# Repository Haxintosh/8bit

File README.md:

# 8bit
8-bit SAP-3 inspired breadboard CPU architecture design using 74xx series logic chips.  
## Files
KiCad design files can be found under `schematic/`, clone and open `8bit.kicad_pro`.  
Schematic PDF is under `schematic/pdf/`.  

Simulation files for Digital can be found under `simulation/`.  
The hex files to program EEPROMs are under `simulation/hex/`.  

Python code to generate ucode bin files is under `code/`, run the `code/generate_roms.py` to generate the files.  

A simple assembly code is under `code/examples/`.  

## Simulation
The project uses the `hneemann/Digital` [Digital](https://github.com/hneemann/digital) simulator.  
Open the `main_manual.dig` in Digital to view the simulation.  
  
Run the simulation and click on the AUTO_EN input for the clock to tick automatically, or you can also click the clock to pulse it manually.  

## Features
- 8 bit wide data bus
- 16 bit wide address bus
- 8 bit A/B/C/D/E/H/L/temporary registers
- BC, DE, HL can pair up to become a 16 bit wide register
- 32k RAM
- Memory-Mapped IO
- 16 bit stack pointer, memory address register, program counter
- 8080-like instruction set
- CompactFlash read/write
- LCD output

## Demo
1. SAP-3 in simulation

2. (Video) SAP-3 running fibonacci code

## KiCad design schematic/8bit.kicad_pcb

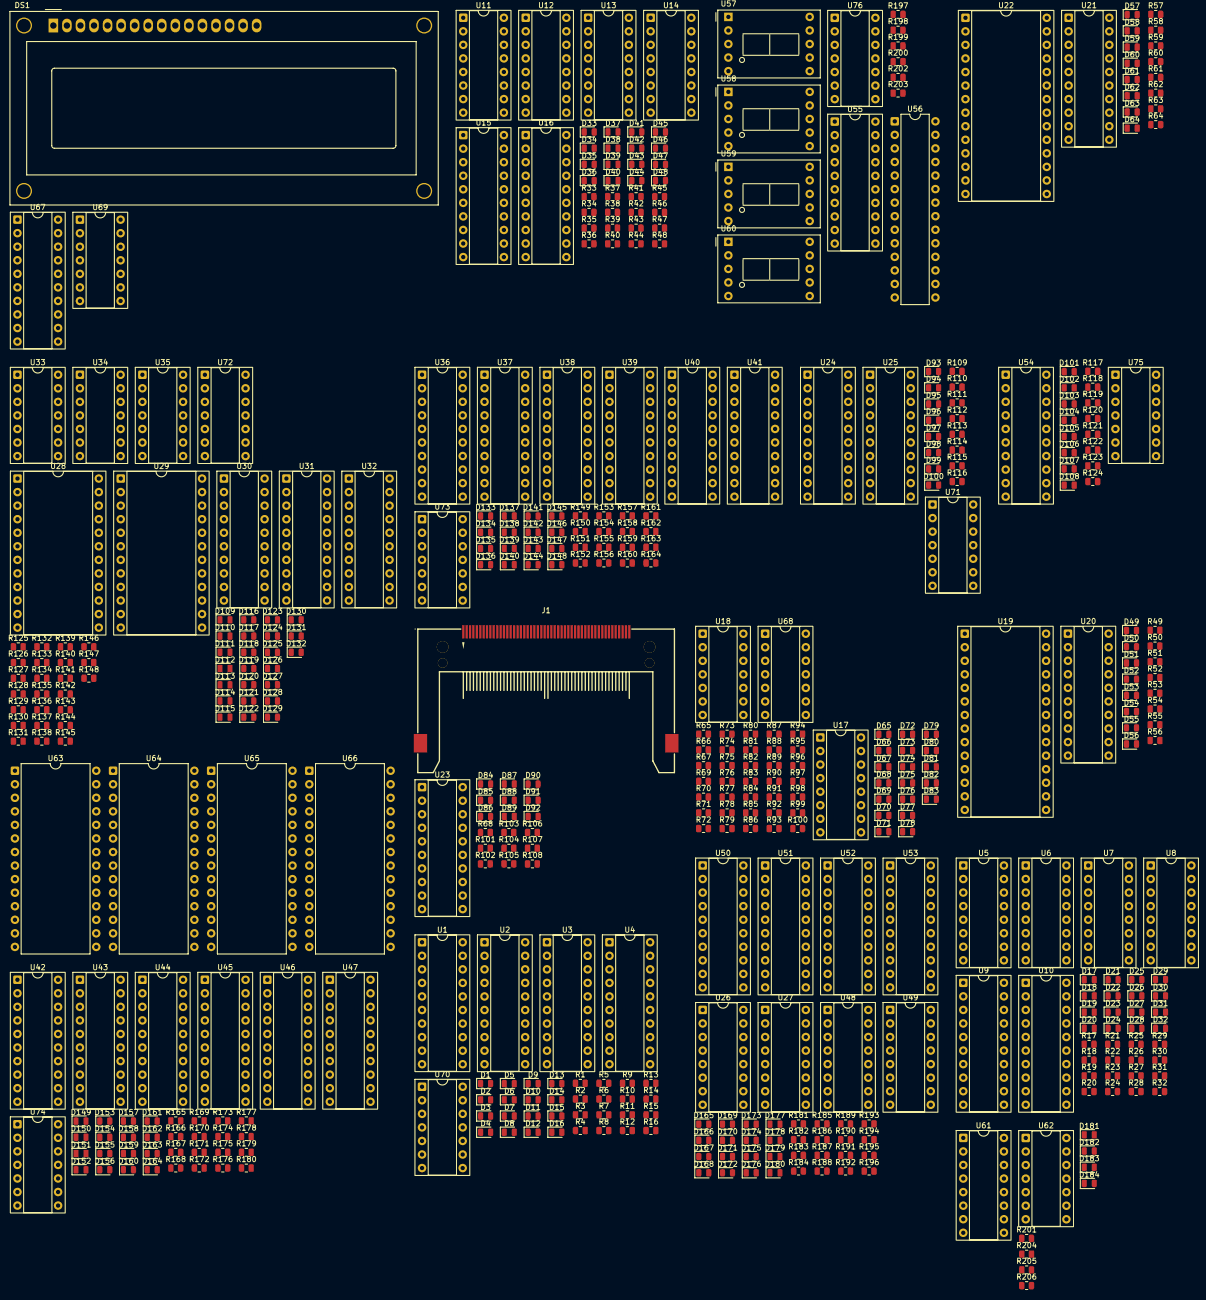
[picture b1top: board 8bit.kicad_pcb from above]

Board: 2 copper layers, 468 parts (0 on the bottom side), 560 nets, no tracks yet.

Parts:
D1, D2, D3, D4, D5, D6, D7, D8, D9, D10, D11, D12, D13, D14, D15, D16, D17, D18, D19, D20, D21, D22, D23, D24, D25, D26, D27, D28, D29, D30, D31, D32, D33, D34, D35, D36, D37, D38, D39, D40, D41, D42, D43, D44, D45, D46, D47, D48, D49, D50, D51, D52, D53, D54, D55, D56, D57, D58, D59, D60, D61, D62, D63, D64, D65, D66, D67, D68, D69, D70, D71, D72, D73, D74, D75, D76, D77, D78, D79, D80, D81, D82, D83, D84, D85, D86, D87, D88, D89, D90, D91, D92, D93, D94, D95, D96, D97, D98, D99, D100, D101, D102, D103, D104, D105, D106, D107, D108, D109, D110, D111, D112, D113, D114, D115, D116, D117, D118, D119, D120, D121, D122, D123, D124, D125, D126, D127, D128, D129, D130, D131, D132, D133, D134, D135, D136, D137, D138, D139, D140, D141, D142, D143, D144, D145, D146, D147, D148, D149, D150, D151, D152, D153, D154, D155, D156, D157, D158, D159, D160, D161, D162, D163, D164, D165, D166, D167, D168, D169, D170, D171, D172, D173, D174, D175, D176, D177, D178, D179, D180, D181, D182, D183, D184: LED; LED_0805_2012Metric
DS1: WC1602A
J1: CF; CONN-SMD_HYCW01-CF50-395B
R1, R2, R3, R4, R5, R6, R7, R8, R9, R10, R11, R12, R13, R14, R15, R16, R17, R18, R19, R20, R21, R22, R23, R24, R25, R26, R27, R28, R29, R30, R31, R32, R33, R34, R35, R36, R37, R38, R39, R40, R41, R42, R43, R44, R45, R46, R47, R48, R49, R50, R51, R52, R53, R54, R55, R56, R57, R58, R59, R60, R61, R62, R63, R64, R65, R66, R67, R68, R70, R72, R74, R76, R78, R80, R82, R84, R86, R88, R90, R92, R94, R96, R98, R100, R101, R102, R103, R104, R105, R106, R107, R108, R109, R110, R111, R112, R113, R114, R115, R116, R117, R118, R119, R120, R121, R122, R123, R124, R125, R126, R127, R128, R129, R130, R131, R132, R133, R134, R135, R136, R137, R138, R139, R140, R141, R142, R143, R144, R145, R146, R147, R148, R149, R150, R151, R152, R153, R154, R155, R156, R157, R158, R159, R160, R161, R162, R163, R164, R165, R166, R167, R168, R169, R170, R171, R172, R173, R174, R175, R176, R177, R178, R179, R180, R181, R182, R183, R184, R185, R186, R187, R188, R189, R190, R191, R192, R193, R194, R195, R196, R201, R204, R205, R206: 470; R_0805_2012Metric
R69, R71, R73, R75, R77, R79, R81, R83, R85, R87, R89, R91, R93, R95, R97, R99: 1k; R_0805_2012Metric
R197, R198, R199, R200, R202: 0; R_0805_2012Metric
R203: 4.7k; R_0805_2012Metric
U1, U2, U24, U32, U36, U38, U42, U43, U54, U55, U67: 74LS573; DIP-20_W7.62mm_Socket
U3, U4, U9, U10, U15, U16, U20, U21, U23, U25, U30, U37, U39, U40, U41, U44, U45, U46, U47, U50, U51, U52, U53: 74LS245; DIP-20_W7.62mm_Socket
U5, U6, U7, U8, U61: 74LS161; DIP-16_W7.62mm_Socket
U11, U12, U13, U14, U26, U27, U48, U49: 74LS193; DIP-16_W7.62mm_Socket
U17: 74LS138; DIP-16_W7.62mm_Socket
U18: 74LS20; DIP-14_W7.62mm_Socket
U19: HM62256BLP; DIP-28_W15.24mm_Socket
U22: KM28C64A; DIP-28_W15.24mm_Socket
U28, U29: 74LS181; DIP-24_W15.24mm_Socket
U31: 74LS373; DIP-20_W7.62mm_Socket
U33, U69, U70, U71, U72, U73, U74, U75, U76: 74LS08; DIP-14_W7.62mm_Socket
U34, U62: 74LS02; DIP-14_W7.62mm_Socket
U35: 74LS04; DIP-14_W7.62mm_Socket
U56: ATmega328-P; DIP-28_W7.62mm
U57, U58, U59, U60: D198K; D1X8K
U63, U64, U65, U66: 27C512; DIP-28_W15.24mm
U68: 74LS00; DIP-14_W7.62mm_Socket

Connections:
+5V: DS1.2 (VDD), DS1.15 (LED(+)), J1.13 (VCC), J1.32 (~CS1), J1.36 (~WE), J1.38 (VCC), R65.1, R66.1, R67.1, R203.1, U1.20 (VCC), U2.20 (VCC), U3.1 (A->B), U3.20 (VCC), U4.1 (A->B), U4.20 (VCC), U5.10 (CET), U5.16 (VCC), U6.16 (VCC), U7.16 (VCC), U8.16 (VCC), U9.1 (A->B), U9.20 (VCC), U10.1 (A->B), U10.20 (VCC), U11.16 (VCC), U12.16 (VCC), U13.16 (VCC), U14.16 (VCC), U15.1 (A->B), U15.20 (VCC), U16.1 (A->B), U16.20 (VCC), U17.6 (E3), U17.16 (VCC), U18.14 (VCC), U19.28 (VCC), U20.20 (VCC), U21.1 (A->B), U21.20 (VCC), U22.27 (~WE), U22.28 (VCC), U23.20 (VCC), U24.20 (VCC), U25.1 (A->B), U25.20 (VCC), U26.16 (VCC), U27.16 (VCC), U28.7 (Cn), U28.24 (VCC), U29.24 (VCC), U30.1 (A->B), U30.20 (VCC), U31.20 (VCC), U32.20 (VCC), U34.14 (VCC), U35.14 (VCC), U36.20 (VCC), U37.1 (A->B), U37.20 (VCC), U38.20 (VCC), U39.1 (A->B), U39.20 (VCC), U40.1 (A->B), U40.20 (VCC), U41.1 (A->B), U41.20 (VCC), U42.20 (VCC), U43.20 (VCC), U44.1 (A->B), U44.20 (VCC), U45.1 (A->B), U45.20 (VCC), U46.1 (A->B), U46.20 (VCC), U47.1 (A->B), U47.20 (VCC), U48.16 (VCC), U49.16 (VCC), U50.1 (A->B), U50.20 (VCC), U51.1 (A->B), U51.20 (VCC), U52.1 (A->B), U52.20 (VCC), U53.1 (A->B), U53.20 (VCC), U54.20 (VCC), U55.20 (VCC), U56.7 (VCC), U56.20 (AVCC), U61.7 (CEP), U61.9 (~PE), U61.10 (CET), U61.16 (VCC), U62.14 (VCC), U63.28 (VCC), U64.28 (VCC), U65.28 (VCC), U66.28 (VCC), U67.20 (VCC), U68.14 (VCC), U69.14 (VCC), U70.14 (VCC), U71.14 (VCC), U72.14 (VCC), U73.14 (VCC), U74.14 (VCC), U75.14 (VCC), U76.14 (VCC)
/ALU/ALU_M: U28.8 (M), U29.8 (M)
/ALU/ALU_S0: U28.6 (S0), U29.6 (S0)
/ALU/ALU_S1: U28.5 (S1), U29.5 (S1)
/ALU/ALU_S2: U28.4 (S2), U29.4 (S2)
/ALU/ALU_S3: U28.3 (S3), U29.3 (S3)
/ALU/BUS_0: U30.18 (B0), U31.3 (D0)
/ALU/BUS_1: U30.17 (B1), U31.4 (D1)
/ALU/BUS_2: U30.16 (B2), U31.7 (D2)
/ALU/BUS_3: U30.15 (B3), U31.8 (D3)
/ALU/BUS_4: U30.14 (B4), U31.13 (D4)
/ALU/BUS_5: U30.13 (B5), U31.14 (D5)
/ALU/BUS_6: U30.12 (B6), U31.17 (D6)
/ALU/BUS_7: U30.11 (B7), U31.18 (D7)
/ALU/CF: R147.1, U32.18 (Q1)
/ALU/CLK: U72.2, U72.5
/ALU/EF: R146.1, U32.17 (Q2)
/ALU/ZF: R148.1, U32.19 (Q0)
/Address Decoder/ADDR_BUS_0: R99.1, R100.1
/Address Decoder/ADDR_BUS_1: R97.1, R98.1
/Address Decoder/ADDR_BUS_2: R95.1, R96.1
/Address Decoder/ADDR_BUS_3: R93.1, R94.1
/Address Decoder/ADDR_BUS_4: R91.1, R92.1
/Address Decoder/ADDR_BUS_5: R89.1, R90.1
/Address Decoder/ADDR_BUS_6: R87.1, R88.1
/Address Decoder/ADDR_BUS_7: R85.1, R86.1
/Address Decoder/ADDR_BUS_8: R83.1, R84.1
/Address Decoder/ADDR_BUS_9: R81.1, R82.1
/Address Decoder/ADDR_BUS_10: R79.1, R80.1
/Address Decoder/ADDR_BUS_11: R77.1, R78.1
/Address Decoder/ADDR_BUS_12: R75.1, R76.1, U18.1
/Address Decoder/ADDR_BUS_13: R73.1, R74.1, U17.1 (A0), U18.2
/Address Decoder/ADDR_BUS_14: R71.1, R72.1, U17.2 (A1), U18.4
/Address Decoder/ADDR_BUS_15: D66.1 (K), R69.1, R70.1, U17.3 (A2), U18.5
/Address Decoder/~CF_CS: D67.1 (K), U17.11 (O4)
/Address Decoder/~RAM_I: U68.1, U68.2
/Address Decoder/~ROM_CS: D65.1 (K), U18.6
/CF reader/~CF_CS: J1.7 (~CS0), U23.19 (CE)
/CF reader/~CF_WR: J1.35 (~IOWR), U23.1 (A->B)
/Instruction Decoder/BUS_0: U63.10 (A0), U64.10 (A0), U65.10 (A0), U66.10 (A0)
/Instruction Decoder/BUS_1: U63.9 (A1), U64.9 (A1), U65.9 (A1), U66.9 (A1)
/Instruction Decoder/BUS_2: U63.8 (A2), U64.8 (A2), U65.8 (A2), U66.8 (A2)
/Instruction Decoder/BUS_3: U63.7 (A3), U64.7 (A3), U65.7 (A3), U66.7 (A3)
/Instruction Decoder/BUS_4: U63.6 (A4), U64.6 (A4), U65.6 (A4), U66.6 (A4)
/Instruction Decoder/BUS_5: U63.5 (A5), U64.5 (A5), U65.5 (A5), U66.5 (A5)
/Instruction Decoder/BUS_6: U63.4 (A6), U64.4 (A6), U65.4 (A6), U66.4 (A6)
/Instruction Decoder/BUS_7: U63.3 (A7), U64.3 (A7), U65.3 (A7), U66.3 (A7)
/Instruction Decoder/CF: U63.2 (A12), U64.2 (A12), U65.2 (A12), U66.2 (A12)
/Instruction Decoder/EF: U63.27 (A14), U64.27 (A14), U65.27 (A14), U66.27 (A14)
/Instruction Decoder/STEP_0: U63.25 (A8), U64.25 (A8), U65.25 (A8), U66.25 (A8)
/Instruction Decoder/STEP_1: U63.24 (A9), U64.24 (A9), U65.24 (A9), U66.24 (A9)
/Instruction Decoder/STEP_2: U63.21 (A10), U64.21 (A10), U65.21 (A10), U66.21 (A10)
/Instruction Decoder/STEP_3: U63.23 (A11), U64.23 (A11), U65.23 (A11), U66.23 (A11)
/Instruction Decoder/ZF: U63.26 (A13), U64.26 (A13), U65.26 (A13), U66.26 (A13)
/Instruction Register/IR_0: R124.1, U54.19 (Q0)
/Instruction Register/IR_1: R123.1, U54.18 (Q1)
/Instruction Register/IR_2: R122.1, U54.17 (Q2)
/Instruction Register/IR_3: R121.1, U54.16 (Q3)
/Instruction Register/IR_4: R120.1, U54.15 (Q4)
/Instruction Register/IR_5: R119.1, U54.14 (Q5)
/Instruction Register/IR_6: R118.1, U54.13 (Q6)
/Instruction Register/IR_7: R117.1, U54.12 (Q7)
/MAR/BUS_0: U1.2 (D0), U2.2 (D0)
/MAR/BUS_1: U1.3 (D1), U2.3 (D1)
/MAR/BUS_2: U1.4 (D2), U2.4 (D2)
/MAR/BUS_3: U1.5 (D3), U2.5 (D3)
/MAR/BUS_4: U1.6 (D4), U2.6 (D4)
/MAR/BUS_5: U1.7 (D5), U2.7 (D5)
/MAR/BUS_6: U1.8 (D6), U2.8 (D6)
/MAR/BUS_7: U1.9 (D7), U2.9 (D7)
/MAR/CLK: U70.2, U70.5
/MAR/~MAR_O: U3.19 (CE), U4.19 (CE)
/Program Counter/BUS_0: U5.3 (D0), U7.3 (D0)
/Program Counter/BUS_1: U5.4 (D1), U7.4 (D1)
/Program Counter/BUS_2: U5.5 (D2), U7.5 (D2)
/Program Counter/BUS_3: U5.6 (D3), U7.6 (D3)
/Program Counter/BUS_4: U6.3 (D0), U8.3 (D0)
/Program Counter/BUS_5: U6.4 (D1), U8.4 (D1)
/Program Counter/BUS_6: U6.5 (D2), U8.5 (D2)
/Program Counter/BUS_7: U6.6 (D3), U8.6 (D3)
/Program Counter/CLK: U5.2 (CP), U6.2 (CP), U7.2 (CP), U8.2 (CP)
/Program Counter/PC_E: U5.7 (CEP), U6.7 (CEP), U7.7 (CEP), U8.7 (CEP)
/Program Counter/~JMP_H: U7.9 (~PE), U8.9 (~PE)
/Program Counter/~JMP_L: U5.9 (~PE), U6.9 (~PE)
/Program Counter/~PC_O: U9.19 (CE), U10.19 (CE)
/Program Counter/~RST: U5.1 (~MR), U6.1 (~MR), U7.1 (~MR), U8.1 (~MR)
/RAM/~RAM_CS: U19.20 (~CS), U20.19 (CE)
/RAM/~RAM_I: U19.27 (~WE), U20.1 (A->B)
/ROM/~ROM_CS: U21.19 (CE), U22.20 (~CE)
/Register A/A_REG_0: R116.1, U24.19 (Q0), U25.2 (A0)
/Register A/A_REG_1: R115.1, U24.18 (Q1), U25.3 (A1)
/Register A/A_REG_2: R114.1, U24.17 (Q2), U25.4 (A2)
/Register A/A_REG_3: R113.1, U24.16 (Q3), U25.5 (A3)
/Register A/A_REG_4: R112.1, U24.15 (Q4), U25.6 (A4)
/Register A/A_REG_5: R111.1, U24.14 (Q5), U25.7 (A5)
/Register A/A_REG_6: R110.1, U24.13 (Q6), U25.8 (A6)
/Register A/A_REG_7: R109.1, U24.12 (Q7), U25.9 (A7)
/Register A/BUS_0: U24.2 (D0), U25.18 (B0)
/Register A/BUS_1: U24.3 (D1), U25.17 (B1)
/Register A/BUS_2: U24.4 (D2), U25.16 (B2)
/Register A/BUS_3: U24.5 (D3), U25.15 (B3)
/Register A/BUS_4: U24.6 (D4), U25.14 (B4)
/Register A/BUS_5: U24.7 (D5), U25.13 (B5)
/Register A/BUS_6: U24.8 (D6), U25.12 (B6)
/Register A/BUS_7: U24.9 (D7), U25.11 (B7)
/Register pair BC/BUS_0: U36.2 (D0), U37.18 (B0), U38.2 (D0), U39.18 (B0)
/Register pair BC/BUS_1: U36.3 (D1), U37.17 (B1), U38.3 (D1), U39.17 (B1)
/Register pair BC/BUS_2: U36.4 (D2), U37.16 (B2), U38.4 (D2), U39.16 (B2)
/Register pair BC/BUS_3: U36.5 (D3), U37.15 (B3), U38.5 (D3), U39.15 (B3)
/Register pair BC/BUS_4: U36.6 (D4), U37.14 (B4), U38.6 (D4), U39.14 (B4)
/Register pair BC/BUS_5: U36.7 (D5), U37.13 (B5), U38.7 (D5), U39.13 (B5)
/Register pair BC/BUS_6: U36.8 (D6), U37.12 (B6), U38.8 (D6), U39.12 (B6)
/Register pair BC/BUS_7: U36.9 (D7), U37.11 (B7), U38.9 (D7), U39.11 (B7)
/Register pair BC/CLK: U73.2, U73.5
/Register pair BC/~PAIR_BC_O: U40.19 (CE), U41.19 (CE)
/Register pair DE/BUS_0: U42.2 (D0), U43.2 (D0), U44.18 (B0), U45.18 (B0)
/Register pair DE/BUS_1: U42.3 (D1), U43.3 (D1), U44.17 (B1), U45.17 (B1)
/Register pair DE/BUS_2: U42.4 (D2), U43.4 (D2), U44.16 (B2), U45.16 (B2)
/Register pair DE/BUS_3: U42.5 (D3), U43.5 (D3), U44.15 (B3), U45.15 (B3)
/Register pair DE/BUS_4: U42.6 (D4), U43.6 (D4), U44.14 (B4), U45.14 (B4)
/Register pair DE/BUS_5: U42.7 (D5), U43.7 (D5), U44.13 (B5), U45.13 (B5)
/Register pair DE/BUS_6: U42.8 (D6), U43.8 (D6), U44.12 (B6), U45.12 (B6)
/Register pair DE/BUS_7: U42.9 (D7), U43.9 (D7), U44.11 (B7), U45.11 (B7)
/Register pair DE/CLK: U74.2, U74.5
/Register pair DE/~PAIR_DE_O: U46.19 (CE), U47.19 (CE)
/Register pair HL/BUS_0: U26.15 (A), U48.15 (A), U52.18 (B0), U53.18 (B0)
/Register pair HL/BUS_1: U26.1 (B), U48.1 (B), U52.17 (B1), U53.17 (B1)
/Register pair HL/BUS_2: U26.10 (C), U48.10 (C), U52.16 (B2), U53.16 (B2)
/Register pair HL/BUS_3: U26.9 (D), U48.9 (D), U52.15 (B3), U53.15 (B3)
/Register pair HL/BUS_4: U27.15 (A), U49.15 (A), U52.14 (B4), U53.14 (B4)
/Register pair HL/BUS_5: U27.1 (B), U49.1 (B), U52.13 (B5), U53.13 (B5)
/Register pair HL/BUS_6: U27.10 (C), U49.10 (C), U52.12 (B6), U53.12 (B6)
/Register pair HL/BUS_7: U27.9 (D), U49.9 (D), U52.11 (B7), U53.11 (B7)
/Register pair HL/RST: U26.14 (CLR), U27.14 (CLR), U48.14 (CLR), U49.14 (CLR)
/Register pair HL/~PAIR_HL_O: U50.19 (CE), U51.19 (CE)
/Register pair HL/~REG_H_I: U48.11 (~LOAD), U49.11 (~LOAD)
/Register pair HL/~REG_L_I: U26.11 (~LOAD), U27.11 (~LOAD)
/Stack Pointer/BUS_0: U11.15 (A), U13.15 (A)
/Stack Pointer/BUS_1: U11.1 (B), U13.1 (B)
/Stack Pointer/BUS_2: U11.10 (C), U13.10 (C)
/Stack Pointer/BUS_3: U11.9 (D), U13.9 (D)
/Stack Pointer/BUS_4: U12.15 (A), U14.15 (A)
/Stack Pointer/BUS_5: U12.1 (B), U14.1 (B)
/Stack Pointer/BUS_6: U12.10 (C), U14.10 (C)
/Stack Pointer/BUS_7: U12.9 (D), U14.9 (D)
/Stack Pointer/RST: U11.14 (CLR), U12.14 (CLR), U13.14 (CLR), U14.14 (CLR)
/Stack Pointer/~SP_H_I: U13.11 (~LOAD), U14.11 (~LOAD)
/Stack Pointer/~SP_L_I: U11.11 (~LOAD), U12.11 (~LOAD)
/Stack Pointer/~SP_O: U15.19 (CE), U16.19 (CE)
/Step Counter/STEP_0: R206.1, U61.14 (Q0)
/Step Counter/STEP_1: R205.1, U61.13 (Q1)
/Step Counter/STEP_2: R204.1, U61.12 (Q2)
/Step Counter/STEP_3: R201.1, U61.11 (Q3)
GND: D1.1 (K), D2.1 (K), D3.1 (K), D4.1 (K), D5.1 (K), D6.1 (K), D7.1 (K), D8.1 (K), D9.1 (K), D10.1 (K), D11.1 (K), D12.1 (K), D13.1 (K), D14.1 (K), D15.1 (K), D16.1 (K), D17.1 (K), D18.1 (K), D19.1 (K), D20.1 (K), D21.1 (K), D22.1 (K), D23.1 (K), D24.1 (K), D25.1 (K), D26.1 (K), D27.1 (K), D28.1 (K), D29.1 (K), D30.1 (K), D31.1 (K), D32.1 (K), D33.1 (K), D34.1 (K), D35.1 (K), D36.1 (K), D37.1 (K), D38.1 (K), D39.1 (K), D40.1 (K), D41.1 (K), D42.1 (K), D43.1 (K), D44.1 (K), D45.1 (K), D46.1 (K), D47.1 (K), D48.1 (K), D49.1 (K), D50.1 (K), D51.1 (K), D52.1 (K), D53.1 (K), D54.1 (K), D55.1 (K), D56.1 (K), D57.1 (K), D58.1 (K), D59.1 (K), D60.1 (K), D61.1 (K), D62.1 (K), D63.1 (K), D64.1 (K), D68.1 (K), D69.1 (K), D70.1 (K), D71.1 (K), D72.1 (K), D73.1 (K), D74.1 (K), D75.1 (K), D76.1 (K), D77.1 (K), D78.1 (K), D79.1 (K), D80.1 (K), D81.1 (K), D82.1 (K), D83.1 (K), D84.1 (K), D85.1 (K), D86.1 (K), D87.1 (K), D88.1 (K), D89.1 (K), D90.1 (K), D91.1 (K), D92.1 (K), D93.1 (K), D94.1 (K), D95.1 (K), D96.1 (K), D97.1 (K), D98.1 (K), D99.1 (K), D100.1 (K), D101.1 (K), D102.1 (K), D103.1 (K), D104.1 (K), D105.1 (K), D106.1 (K), D107.1 (K), D108.1 (K), D109.1 (K), D110.1 (K), D111.1 (K), D112.1 (K), D113.1 (K), D114.1 (K), D115.1 (K), D116.1 (K), D117.1 (K), D118.1 (K), D119.1 (K), D120.1 (K), D121.1 (K), D122.1 (K), D123.1 (K), D124.1 (K), D125.1 (K), D126.1 (K), D127.1 (K), D128.1 (K), D129.1 (K), D130.1 (K), D131.1 (K), D132.1 (K), D133.1 (K), D134.1 (K), D135.1 (K), D136.1 (K), D137.1 (K), D138.1 (K), D139.1 (K), D140.1 (K), D141.1 (K), D142.1 (K), D143.1 (K), D144.1 (K), D145.1 (K), D146.1 (K), D147.1 (K), D148.1 (K), D149.1 (K), D150.1 (K), D151.1 (K), D152.1 (K), D153.1 (K), D154.1 (K), D155.1 (K), D156.1 (K), D157.1 (K), D158.1 (K), D159.1 (K), D160.1 (K), D161.1 (K), D162.1 (K), D163.1 (K), D164.1 (K), D165.1 (K), D166.1 (K), D167.1 (K), D168.1 (K), D169.1 (K), D170.1 (K), D171.1 (K), D172.1 (K), D173.1 (K), D174.1 (K), D175.1 (K), D176.1 (K), D177.1 (K), D178.1 (K), D179.1 (K), D180.1 (K), D181.1 (K), D182.1 (K), D183.1 (K), D184.1 (K), DS1.1 (VSS), DS1.5 (R/W), DS1.16 (LED(-)), J1.0 (GND), J1.1 (GND), J1.9 (~ATA_SEL), J1.50 (GND), R69.2, R71.2, R73.2, R75.2, R77.2, R79.2, R81.2, R83.2, R85.2, R87.2, R89.2, R91.2, R93.2, R95.2, R97.2, R99.2, U1.1 (OE), U1.10 (GND), U2.1 (OE), U2.10 (GND), U3.10 (GND), U4.10 (GND), U5.8 (GND), U6.8 (GND), U7.8 (GND), U8.8 (GND), U9.10 (GND), U10.10 (GND), U11.8 (GND), U12.8 (GND), U13.8 (GND), U14.8 (GND), U15.10 (GND), U16.10 (GND), U17.4 (E1), U17.5 (E2), U17.8 (GND), U18.7 (GND), U19.14 (GND), U19.22 (~OE), U20.10 (GND), U21.10 (GND), U22.14 (GND), U22.22 (~OE), U23.10 (GND), U24.1 (OE), U24.10 (GND), U25.10 (GND), U26.8 (GND), U27.8 (GND), U28.12 (GND), U29.12 (GND), U30.10 (GND), U31.1 (OE), U31.10 (GND), U32.1 (OE), U32.10 (GND), U34.7 (GND), U35.7 (GND), U36.1 (OE), U36.10 (GND), U37.10 (GND), U38.1 (OE), U38.10 (GND), U39.10 (GND), U40.10 (GND), U41.10 (GND), U42.1 (OE), U42.10 (GND), U43.1 (OE), U43.10 (GND), U44.10 (GND), U45.10 (GND), U46.10 (GND), U47.10 (GND), U48.8 (GND), U49.8 (GND), U50.10 (GND), U51.10 (GND), U52.10 (GND), U53.10 (GND), U54.1 (OE), U54.10 (GND), U55.1 (OE), U55.10 (GND), U56.8 (GND), U56.22 (GND), U61.8 (GND), U62.7 (GND), U63.14 (GND), U63.20 (~CE), U63.22 (~OE), U64.14 (GND), U64.20 (~CE), U64.22 (~OE), U65.14 (GND), U65.20 (~CE), U65.22 (~OE), U66.14 (GND), U66.20 (~CE), U66.22 (~OE), U67.1 (OE), U67.10 (GND), U68.7 (GND), U69.7 (GND), U70.7 (GND), U71.7 (GND), U72.7 (GND), U73.7 (GND), U74.7 (GND), U75.7 (GND), U76.7 (GND)
unnamed: D1.2 (A), R1.2
unnamed: D2.2 (A), R2.2
unnamed: D3.2 (A), R3.2
unnamed: D4.2 (A), R4.2
unnamed: D5.2 (A), R5.2
unnamed: D6.2 (A), R6.2
unnamed: D7.2 (A), R7.2
unnamed: D8.2 (A), R8.2
unnamed: D9.2 (A), R9.2
unnamed: D10.2 (A), R10.2
unnamed: D11.2 (A), R11.2
unnamed: D12.2 (A), R12.2
unnamed: D13.2 (A), R13.2
unnamed: D14.2 (A), R14.2
unnamed: D15.2 (A), R15.2
unnamed: D16.2 (A), R16.2
unnamed: D17.2 (A), R17.2
unnamed: D18.2 (A), R18.2
unnamed: D19.2 (A), R19.2
unnamed: D20.2 (A), R20.2
unnamed: D21.2 (A), R21.2
unnamed: D22.2 (A), R22.2
unnamed: D23.2 (A), R23.2
unnamed: D24.2 (A), R24.2
unnamed: D25.2 (A), R25.2
unnamed: D26.2 (A), R26.2
unnamed: D27.2 (A), R27.2
unnamed: D28.2 (A), R28.2
unnamed: D29.2 (A), R29.2
unnamed: D30.2 (A), R30.2
unnamed: D31.2 (A), R31.2
unnamed: D32.2 (A), R32.2
unnamed: D33.2 (A), R33.2
unnamed: D34.2 (A), R34.2
unnamed: D35.2 (A), R35.2
unnamed: D36.2 (A), R36.2
unnamed: D37.2 (A), R37.2
unnamed: D38.2 (A), R38.2
unnamed: D39.2 (A), R39.2
unnamed: D40.2 (A), R40.2
unnamed: D41.2 (A), R41.2
unnamed: D42.2 (A), R42.2
unnamed: D43.2 (A), R43.2
unnamed: D44.2 (A), R44.2
unnamed: D45.2 (A), R45.2
unnamed: D46.2 (A), R46.2
unnamed: D47.2 (A), R47.2
unnamed: D48.2 (A), R48.2
unnamed: D49.2 (A), R49.2
unnamed: D50.2 (A), R50.2
unnamed: D51.2 (A), R51.2
unnamed: D52.2 (A), R52.2
unnamed: D53.2 (A), R53.2
unnamed: D54.2 (A), R54.2
unnamed: D55.2 (A), R55.2
unnamed: D56.2 (A), R56.2
unnamed: D57.2 (A), R57.2
unnamed: D58.2 (A), R58.2
unnamed: D59.2 (A), R59.2
unnamed: D60.2 (A), R60.2
unnamed: D61.2 (A), R61.2
unnamed: D62.2 (A), R62.2
unnamed: D63.2 (A), R63.2
unnamed: D64.2 (A), R64.2
unnamed: D65.2 (A), R65.2
unnamed: D66.2 (A), R66.2
unnamed: D67.2 (A), R67.2
unnamed: D68.2 (A), R70.2
unnamed: D69.2 (A), R72.2
unnamed: D70.2 (A), R74.2
unnamed: D71.2 (A), R76.2
unnamed: D72.2 (A), R78.2
unnamed: D73.2 (A), R80.2
unnamed: D74.2 (A), R82.2
unnamed: D75.2 (A), R84.2
unnamed: D76.2 (A), R86.2
unnamed: D77.2 (A), R88.2
unnamed: D78.2 (A), R90.2
unnamed: D79.2 (A), R92.2
unnamed: D80.2 (A), R94.2
unnamed: D81.2 (A), R96.2
unnamed: D82.2 (A), R98.2
unnamed: D83.2 (A), R100.2
unnamed: D84.2 (A), R68.2
unnamed: D85.2 (A), R101.2
unnamed: D86.2 (A), R102.2
unnamed: D87.2 (A), R103.2
unnamed: D88.2 (A), R104.2
unnamed: D89.2 (A), R105.2
unnamed: D90.2 (A), R106.2
unnamed: D91.2 (A), R107.2
unnamed: D92.2 (A), R108.2
unnamed: D93.2 (A), R109.2
unnamed: D94.2 (A), R110.2
unnamed: D95.2 (A), R111.2
unnamed: D96.2 (A), R112.2
unnamed: D97.2 (A), R113.2
unnamed: D98.2 (A), R114.2
unnamed: D99.2 (A), R115.2
unnamed: D100.2 (A), R116.2
unnamed: D101.2 (A), R117.2
unnamed: D102.2 (A), R118.2
unnamed: D103.2 (A), R119.2
unnamed: D104.2 (A), R120.2
unnamed: D105.2 (A), R121.2
unnamed: D106.2 (A), R122.2
unnamed: D107.2 (A), R123.2
unnamed: D108.2 (A), R124.2
unnamed: D109.2 (A), R125.2
unnamed: D110.2 (A), R126.2
unnamed: D111.2 (A), R127.2
unnamed: D112.2 (A), R128.2
unnamed: D113.2 (A), R129.2
unnamed: D114.2 (A), R130.2
unnamed: D115.2 (A), R131.2
unnamed: D116.2 (A), R132.2
unnamed: D117.2 (A), R133.2
unnamed: D118.2 (A), R134.2
unnamed: D119.2 (A), R135.2
unnamed: D120.2 (A), R136.2
unnamed: D121.2 (A), R137.2
unnamed: D122.2 (A), R138.2
unnamed: D123.2 (A), R139.2
unnamed: D124.2 (A), R140.2
unnamed: D125.2 (A), R141.2
unnamed: D126.2 (A), R142.2
unnamed: D127.2 (A), R143.2
unnamed: D128.2 (A), R144.2
unnamed: D129.2 (A), R145.2
unnamed: D130.2 (A), R146.2
unnamed: D131.2 (A), R147.2
unnamed: D132.2 (A), R148.2
unnamed: D133.2 (A), R149.2
unnamed: D134.2 (A), R150.2
unnamed: D135.2 (A), R151.2
unnamed: D136.2 (A), R152.2
unnamed: D137.2 (A), R153.2
unnamed: D138.2 (A), R154.2
unnamed: D139.2 (A), R155.2
unnamed: D140.2 (A), R156.2
unnamed: D141.2 (A), R157.2
unnamed: D142.2 (A), R158.2
unnamed: D143.2 (A), R159.2
unnamed: D144.2 (A), R160.2
unnamed: D145.2 (A), R161.2
unnamed: D146.2 (A), R162.2
unnamed: D147.2 (A), R163.2
unnamed: D148.2 (A), R164.2
unnamed: D149.2 (A), R165.2
unnamed: D150.2 (A), R166.2
unnamed: D151.2 (A), R167.2
unnamed: D152.2 (A), R168.2
unnamed: D153.2 (A), R169.2
unnamed: D154.2 (A), R170.2
unnamed: D155.2 (A), R171.2
unnamed: D156.2 (A), R172.2
unnamed: D157.2 (A), R173.2
unnamed: D158.2 (A), R174.2
unnamed: D159.2 (A), R175.2
unnamed: D160.2 (A), R176.2
unnamed: D161.2 (A), R177.2
unnamed: D162.2 (A), R178.2
unnamed: D163.2 (A), R179.2
unnamed: D164.2 (A), R180.2
unnamed: D165.2 (A), R181.2
unnamed: D166.2 (A), R182.2
unnamed: D167.2 (A), R183.2
unnamed: D168.2 (A), R184.2
unnamed: D169.2 (A), R185.2
unnamed: D170.2 (A), R186.2
unnamed: D171.2 (A), R187.2
unnamed: D172.2 (A), R188.2
unnamed: D173.2 (A), R189.2
unnamed: D174.2 (A), R190.2
unnamed: D175.2 (A), R191.2
unnamed: D176.2 (A), R192.2
unnamed: D177.2 (A), R193.2
unnamed: D178.2 (A), R194.2
unnamed: D179.2 (A), R195.2
unnamed: D180.2 (A), R196.2
unnamed: D181.2 (A), R201.2
unnamed: D182.2 (A), R204.2
unnamed: D183.2 (A), R205.2
unnamed: D184.2 (A), R206.2
unnamed: DS1.7 (D0), U67.19 (Q0)
unnamed: DS1.8 (D1), U67.18 (Q1)
unnamed: DS1.9 (D2), U67.17 (Q2)
unnamed: DS1.10 (D3), U67.16 (Q3)
unnamed: DS1.11 (D4), U67.15 (Q4)
unnamed: DS1.12 (D5), U67.14 (Q5)
unnamed: DS1.13 (D6), U67.13 (Q6)
unnamed: DS1.14 (D7), U67.12 (Q7)
unnamed: J1.21 (D00), R108.1, U23.2 (A0)
unnamed: J1.22 (D01), R107.1, U23.3 (A1)
unnamed: J1.23 (D02), R106.1, U23.4 (A2)
unnamed: J1.2 (D03), R105.1, U23.5 (A3)
unnamed: J1.3 (D04), R104.1, U23.6 (A4)
unnamed: J1.4 (D05), R103.1, U23.7 (A5)
unnamed: J1.5 (D06), R102.1, U23.8 (A6)
unnamed: J1.6 (D07), R101.1, U23.9 (A7)
unnamed: J1.42 (IORDY), R68.1
unnamed: R197.2, U57.3 (CC), U57.8 (CC)
unnamed: R198.2, U58.3 (CC), U58.8 (CC)
unnamed: R199.2, U59.3 (CC), U59.8 (CC)
unnamed: R200.1, U60.3 (CC), U60.8 (CC)
unnamed: U1.11 (Load), U70.3
unnamed: R16.1, U1.19 (Q0), U3.2 (A0)
unnamed: R15.1, U1.18 (Q1), U3.3 (A1)
unnamed: R14.1, U1.17 (Q2), U3.4 (A2)
unnamed: R13.1, U1.16 (Q3), U3.5 (A3)
unnamed: R12.1, U1.15 (Q4), U3.6 (A4)
unnamed: R11.1, U1.14 (Q5), U3.7 (A5)
unnamed: R10.1, U1.13 (Q6), U3.8 (A6)
unnamed: R9.1, U1.12 (Q7), U3.9 (A7)
unnamed: U2.11 (Load), U70.6
unnamed: R8.1, U2.19 (Q0), U4.2 (A0)
unnamed: R7.1, U2.18 (Q1), U4.3 (A1)
unnamed: R6.1, U2.17 (Q2), U4.4 (A2)
unnamed: R5.1, U2.16 (Q3), U4.5 (A3)
unnamed: R4.1, U2.15 (Q4), U4.6 (A4)
unnamed: R3.1, U2.14 (Q5), U4.7 (A5)
unnamed: R2.1, U2.13 (Q6), U4.8 (A6)
unnamed: R1.1, U2.12 (Q7), U4.9 (A7)
unnamed: R32.1, U5.14 (Q0), U9.2 (A0)
unnamed: R31.1, U5.13 (Q1), U9.3 (A1)
unnamed: R30.1, U5.12 (Q2), U9.4 (A2)
unnamed: R29.1, U5.11 (Q3), U9.5 (A3)
unnamed: U5.15 (TC), U6.10 (CET)
unnamed: R28.1, U6.14 (Q0), U9.6 (A4)
unnamed: R27.1, U6.13 (Q1), U9.7 (A5)
unnamed: R26.1, U6.12 (Q2), U9.8 (A6)
unnamed: R25.1, U6.11 (Q3), U9.9 (A7)
unnamed: U6.15 (TC), U7.10 (CET)
unnamed: U7.15 (TC), U8.10 (CET)
unnamed: R24.1, U7.14 (Q0), U10.2 (A0)
unnamed: R23.1, U7.13 (Q1), U10.3 (A1)
unnamed: R22.1, U7.12 (Q2), U10.4 (A2)
unnamed: R21.1, U7.11 (Q3), U10.5 (A3)
unnamed: R20.1, U8.14 (Q0), U10.6 (A4)
unnamed: R19.1, U8.13 (Q1), U10.7 (A5)
unnamed: R18.1, U8.12 (Q2), U10.8 (A6)
unnamed: R17.1, U8.11 (Q3), U10.9 (A7)
unnamed: R48.1, U11.3 (QA), U15.2 (A0)
unnamed: R47.1, U11.2 (QB), U15.3 (A1)
unnamed: R46.1, U11.6 (QC), U15.4 (A2)
unnamed: R45.1, U11.7 (QD), U15.5 (A3)
unnamed: U11.13 (~BO), U12.4 (DOWN)
unnamed: U11.12 (~CO), U12.5 (UP)
unnamed: R44.1, U12.3 (QA), U15.6 (A4)
unnamed: R43.1, U12.2 (QB), U15.7 (A5)
unnamed: R42.1, U12.6 (QC), U15.8 (A6)
unnamed: R41.1, U12.7 (QD), U15.9 (A7)
unnamed: U12.13 (~BO), U13.4 (DOWN)
unnamed: U12.12 (~CO), U13.5 (UP)
unnamed: R40.1, U13.3 (QA), U16.2 (A0)
unnamed: R39.1, U13.2 (QB), U16.3 (A1)
unnamed: R38.1, U13.6 (QC), U16.4 (A2)
unnamed: R37.1, U13.7 (QD), U16.5 (A3)
unnamed: U13.13 (~BO), U14.4 (DOWN)
unnamed: U13.12 (~CO), U14.5 (UP)
unnamed: R36.1, U14.3 (QA), U16.6 (A4)
unnamed: R35.1, U14.2 (QB), U16.7 (A5)
unnamed: R34.1, U14.6 (QC), U16.8 (A6)
unnamed: R33.1, U14.7 (QD), U16.9 (A7)
unnamed: U17.10 (O5), U68.4
unnamed: R56.1, U19.11 (Q0), U20.2 (A0)
unnamed: R55.1, U19.12 (Q1), U20.3 (A1)
unnamed: R54.1, U19.13 (Q2), U20.4 (A2)
unnamed: R53.1, U19.15 (Q3), U20.5 (A3)
unnamed: R52.1, U19.16 (Q4), U20.6 (A4)
unnamed: R51.1, U19.17 (Q5), U20.7 (A5)
unnamed: R50.1, U19.18 (Q6), U20.8 (A6)
unnamed: R49.1, U19.19 (Q7), U20.9 (A7)
unnamed: R64.1, U21.2 (A0), U22.11 (I/O0)
unnamed: R63.1, U21.3 (A1), U22.12 (I/O1)
unnamed: R62.1, U21.4 (A2), U22.13 (I/O2)
unnamed: R61.1, U21.5 (A3), U22.15 (I/O3)
unnamed: R60.1, U21.6 (A4), U22.16 (I/O4)
unnamed: R59.1, U21.7 (A5), U22.17 (I/O5)
unnamed: R58.1, U21.8 (A6), U22.18 (I/O6)
unnamed: R57.1, U21.9 (A7), U22.19 (I/O7)
unnamed: U24.11 (Load), U71.3
unnamed: R188.1, U26.3 (QA), U50.2 (A0), U52.2 (A0)
unnamed: R187.1, U26.2 (QB), U50.3 (A1), U52.3 (A1)
unnamed: R186.1, U26.6 (QC), U50.4 (A2), U52.4 (A2)
unnamed: R185.1, U26.7 (QD), U50.5 (A3), U52.5 (A3)
unnamed: U26.13 (~BO), U27.4 (DOWN)
unnamed: U26.12 (~CO), U27.5 (UP)
unnamed: R184.1, U27.3 (QA), U50.6 (A4), U52.6 (A4)
unnamed: R183.1, U27.2 (QB), U50.7 (A5), U52.7 (A5)
unnamed: R182.1, U27.6 (QC), U50.8 (A6), U52.8 (A6)
unnamed: R181.1, U27.7 (QD), U50.9 (A7), U52.9 (A7)
unnamed: U27.13 (~BO), U48.4 (DOWN)
unnamed: U27.12 (~CO), U48.5 (UP)
unnamed: R140.1, U28.1 (B0), U31.2 (O0)
unnamed: R139.1, U28.22 (B1), U31.5 (O1)
unnamed: R138.1, U28.20 (B2), U31.6 (O2)
unnamed: R137.1, U28.18 (B3), U31.9 (O3)
unnamed: U28.16 (Cn+4), U29.7 (Cn)
unnamed: R132.1, U28.9 (F0), U30.2 (A0), U34.11
unnamed: R131.1, U28.10 (F1), U30.3 (A1), U34.12
unnamed: R130.1, U28.11 (F2), U30.4 (A2), U34.8
unnamed: R129.1, U28.13 (F3), U30.5 (A3), U34.9
unnamed: U29.14 (A=B), U32.4 (D2)
unnamed: R136.1, U29.1 (B0), U31.12 (O4)
unnamed: R135.1, U29.22 (B1), U31.15 (O5)
unnamed: R134.1, U29.20 (B2), U31.16 (O6)
unnamed: R133.1, U29.18 (B3), U31.19 (O7)
unnamed: U29.16 (Cn+4), U35.1
unnamed: R128.1, U29.9 (F0), U30.6 (A4), U34.5
unnamed: R127.1, U29.10 (F1), U30.7 (A5), U34.6
unnamed: R126.1, U29.11 (F2), U30.8 (A6), U34.2
unnamed: R125.1, U29.13 (F3), U30.9 (A7), U34.3
unnamed: U31.11 (LE), U72.6
unnamed: U32.2 (D0), U33.8
unnamed: U32.3 (D1), U35.2
unnamed: U32.11 (Load), U72.3
unnamed: R145.1, U32.16 (Q3)
unnamed: R144.1, U32.15 (Q4)
unnamed: R143.1, U32.14 (Q5)
unnamed: R142.1, U32.13 (Q6)
unnamed: R141.1, U32.12 (Q7)
unnamed: U33.1, U34.4
unnamed: U33.2, U34.1
unnamed: U33.4, U34.13
unnamed: U33.5, U34.10
unnamed: U33.6, U33.9
unnamed: U33.3, U33.10
unnamed: U36.11 (Load), U73.3
unnamed: R156.1, U36.19 (Q0), U37.2 (A0), U40.2 (A0)
unnamed: R155.1, U36.18 (Q1), U37.3 (A1), U40.3 (A1)
unnamed: R154.1, U36.17 (Q2), U37.4 (A2), U40.4 (A2)
unnamed: R153.1, U36.16 (Q3), U37.5 (A3), U40.5 (A3)
unnamed: R152.1, U36.15 (Q4), U37.6 (A4), U40.6 (A4)
unnamed: R151.1, U36.14 (Q5), U37.7 (A5), U40.7 (A5)
unnamed: R150.1, U36.13 (Q6), U37.8 (A6), U40.8 (A6)
unnamed: R149.1, U36.12 (Q7), U37.9 (A7), U40.9 (A7)
unnamed: U38.11 (Load), U73.6
unnamed: R164.1, U38.19 (Q0), U39.2 (A0), U41.2 (A0)
unnamed: R163.1, U38.18 (Q1), U39.3 (A1), U41.3 (A1)
unnamed: R162.1, U38.17 (Q2), U39.4 (A2), U41.4 (A2)
unnamed: R161.1, U38.16 (Q3), U39.5 (A3), U41.5 (A3)
unnamed: R160.1, U38.15 (Q4), U39.6 (A4), U41.6 (A4)
unnamed: R159.1, U38.14 (Q5), U39.7 (A5), U41.7 (A5)
unnamed: R158.1, U38.13 (Q6), U39.8 (A6), U41.8 (A6)
unnamed: R157.1, U38.12 (Q7), U39.9 (A7), U41.9 (A7)
unnamed: U42.11 (Load), U74.3
unnamed: R179.1, U42.19 (Q0), U44.2 (A0), U46.2 (A0)
unnamed: R177.1, U42.18 (Q1), U44.3 (A1), U46.3 (A1)
unnamed: R175.1, U42.17 (Q2), U44.4 (A2), U46.4 (A2)
unnamed: R173.1, U42.16 (Q3), U44.5 (A3), U46.5 (A3)
unnamed: R171.1, U42.15 (Q4), U44.6 (A4), U46.6 (A4)
unnamed: R169.1, U42.14 (Q5), U44.7 (A5), U46.7 (A5)
unnamed: R167.1, U42.13 (Q6), U44.8 (A6), U46.8 (A6)
unnamed: R165.1, U42.12 (Q7), U44.9 (A7), U46.9 (A7)
unnamed: U43.11 (Load), U74.6
unnamed: R180.1, U43.19 (Q0), U45.2 (A0), U47.2 (A0)
unnamed: R178.1, U43.18 (Q1), U45.3 (A1), U47.3 (A1)
unnamed: R176.1, U43.17 (Q2), U45.4 (A2), U47.4 (A2)
unnamed: R174.1, U43.16 (Q3), U45.5 (A3), U47.5 (A3)
unnamed: R172.1, U43.15 (Q4), U45.6 (A4), U47.6 (A4)
unnamed: R170.1, U43.14 (Q5), U45.7 (A5), U47.7 (A5)
unnamed: R168.1, U43.13 (Q6), U45.8 (A6), U47.8 (A6)
unnamed: R166.1, U43.12 (Q7), U45.9 (A7), U47.9 (A7)
unnamed: R196.1, U48.3 (QA), U51.2 (A0), U53.2 (A0)
unnamed: R195.1, U48.2 (QB), U51.3 (A1), U53.3 (A1)
unnamed: R194.1, U48.6 (QC), U51.4 (A2), U53.4 (A2)
unnamed: R193.1, U48.7 (QD), U51.5 (A3), U53.5 (A3)
unnamed: U48.13 (~BO), U49.4 (DOWN)
unnamed: U48.12 (~CO), U49.5 (UP)
unnamed: R192.1, U49.3 (QA), U51.6 (A4), U53.6 (A4)
unnamed: R191.1, U49.2 (QB), U51.7 (A5), U53.7 (A5)
unnamed: R190.1, U49.6 (QC), U51.8 (A6), U53.8 (A6)
unnamed: R189.1, U49.7 (QD), U51.9 (A7), U53.9 (A7)
unnamed: U54.11 (Load), U75.3
unnamed: U55.11 (Load), U76.3
unnamed: U55.19 (Q0), U56.2 (PD0)
unnamed: U55.18 (Q1), U56.3 (PD1)
unnamed: U55.17 (Q2), U56.4 (PD2)
unnamed: U55.16 (Q3), U56.5 (PD3)
unnamed: U55.15 (Q4), U56.6 (PD4)
unnamed: U55.14 (Q5), U56.11 (PD5)
unnamed: U55.13 (Q6), U56.12 (PD6)
unnamed: U55.12 (Q7), U56.13 (PD7)
unnamed: U56.14 (PB0), U57.7 (A), U58.7 (A), U59.7 (A), U60.7 (A)
unnamed: U56.15 (PB1), U57.6 (B), U58.6 (B), U59.6 (B), U60.6 (B)
unnamed: U56.16 (PB2), U57.4 (C), U58.4 (C), U59.4 (C), U60.4 (C)
unnamed: U56.17 (PB3), U57.2 (D), U58.2 (D), U59.2 (D), U60.2 (D)
unnamed: U56.18 (PB4), U57.1 (E), U58.1 (E), U59.1 (E), U60.1 (E)
unnamed: U56.19 (PB5), U57.9 (F), U58.9 (F), U59.9 (F), U60.9 (F)
unnamed: R197.1, U56.23 (PC0)
unnamed: R198.1, U56.24 (PC1)
unnamed: R199.1, U56.25 (PC2)
unnamed: R200.2, U56.26 (PC3)
unnamed: U56.9 (XTAL1/PB6), U57.10 (G), U58.10 (G), U59.10 (G), U60.10 (G)
unnamed: U56.10 (XTAL2/PB7), U57.5 (DP), U58.5 (DP), U59.5 (DP), U60.5 (DP)
unnamed: R202.1, R203.2, U56.1 (~RESET/PC6)
unnamed: U61.15 (TC), U62.12
unnamed: U61.1 (~MR), U62.1
unnamed: U62.2, U62.3, U62.4
unnamed: U62.6, U62.10
unnamed: U62.8, U62.9, U62.13
unnamed: U63.1 (A15), U64.1 (A15), U65.1 (A15), U66.1 (A15)
unnamed: U67.11 (Load), U69.3
unnamed: U68.3, U68.5
unnamed: U68.6, U68.9, U68.10
